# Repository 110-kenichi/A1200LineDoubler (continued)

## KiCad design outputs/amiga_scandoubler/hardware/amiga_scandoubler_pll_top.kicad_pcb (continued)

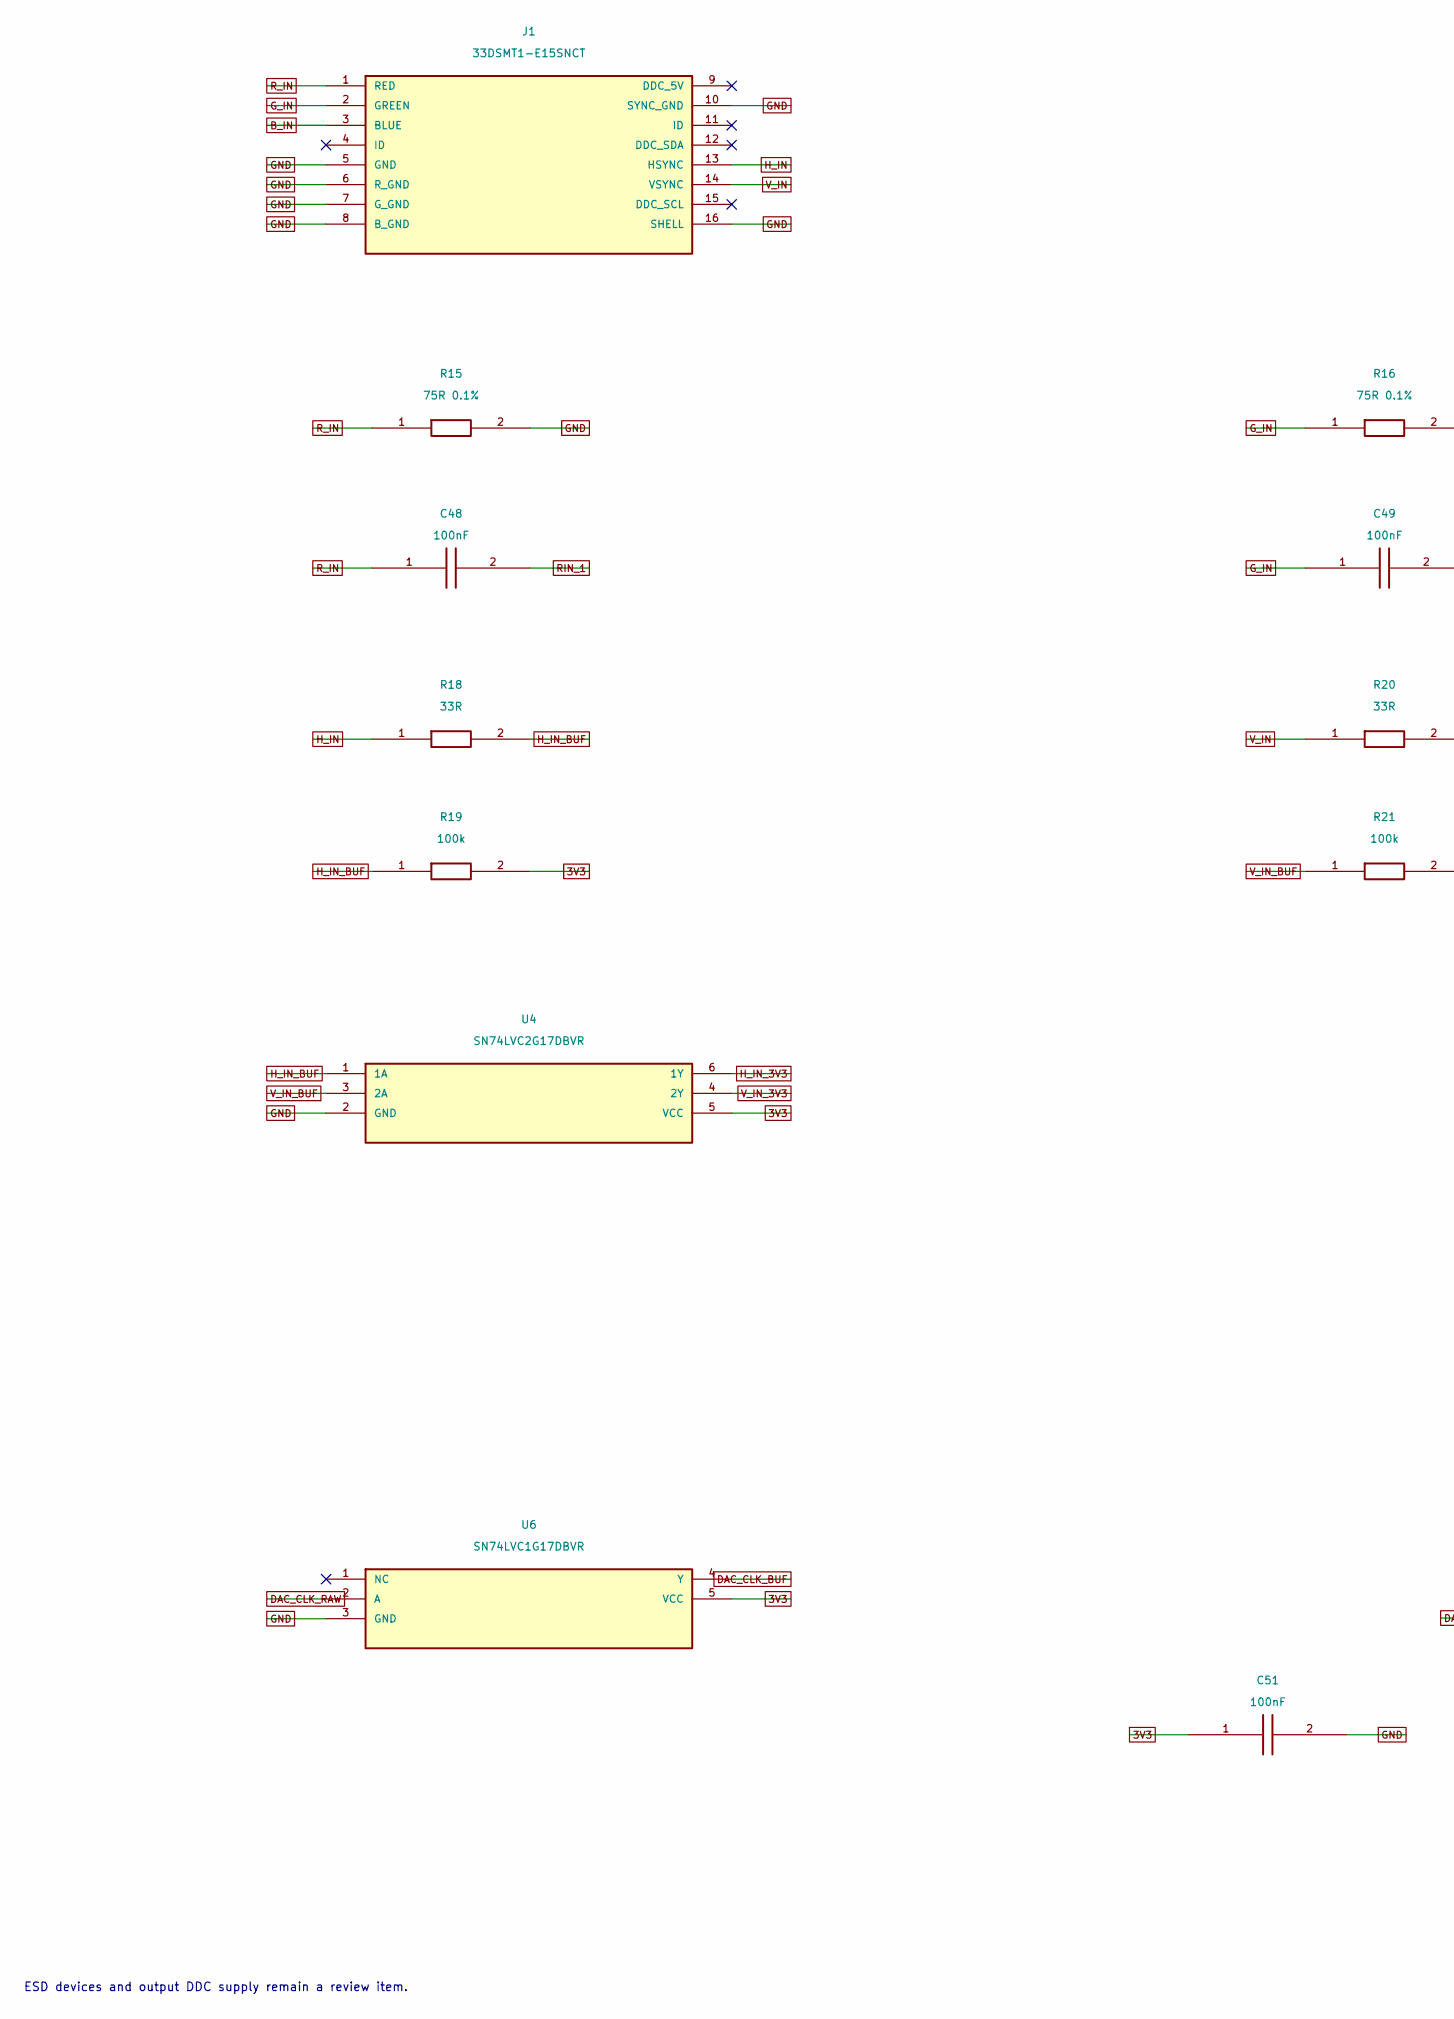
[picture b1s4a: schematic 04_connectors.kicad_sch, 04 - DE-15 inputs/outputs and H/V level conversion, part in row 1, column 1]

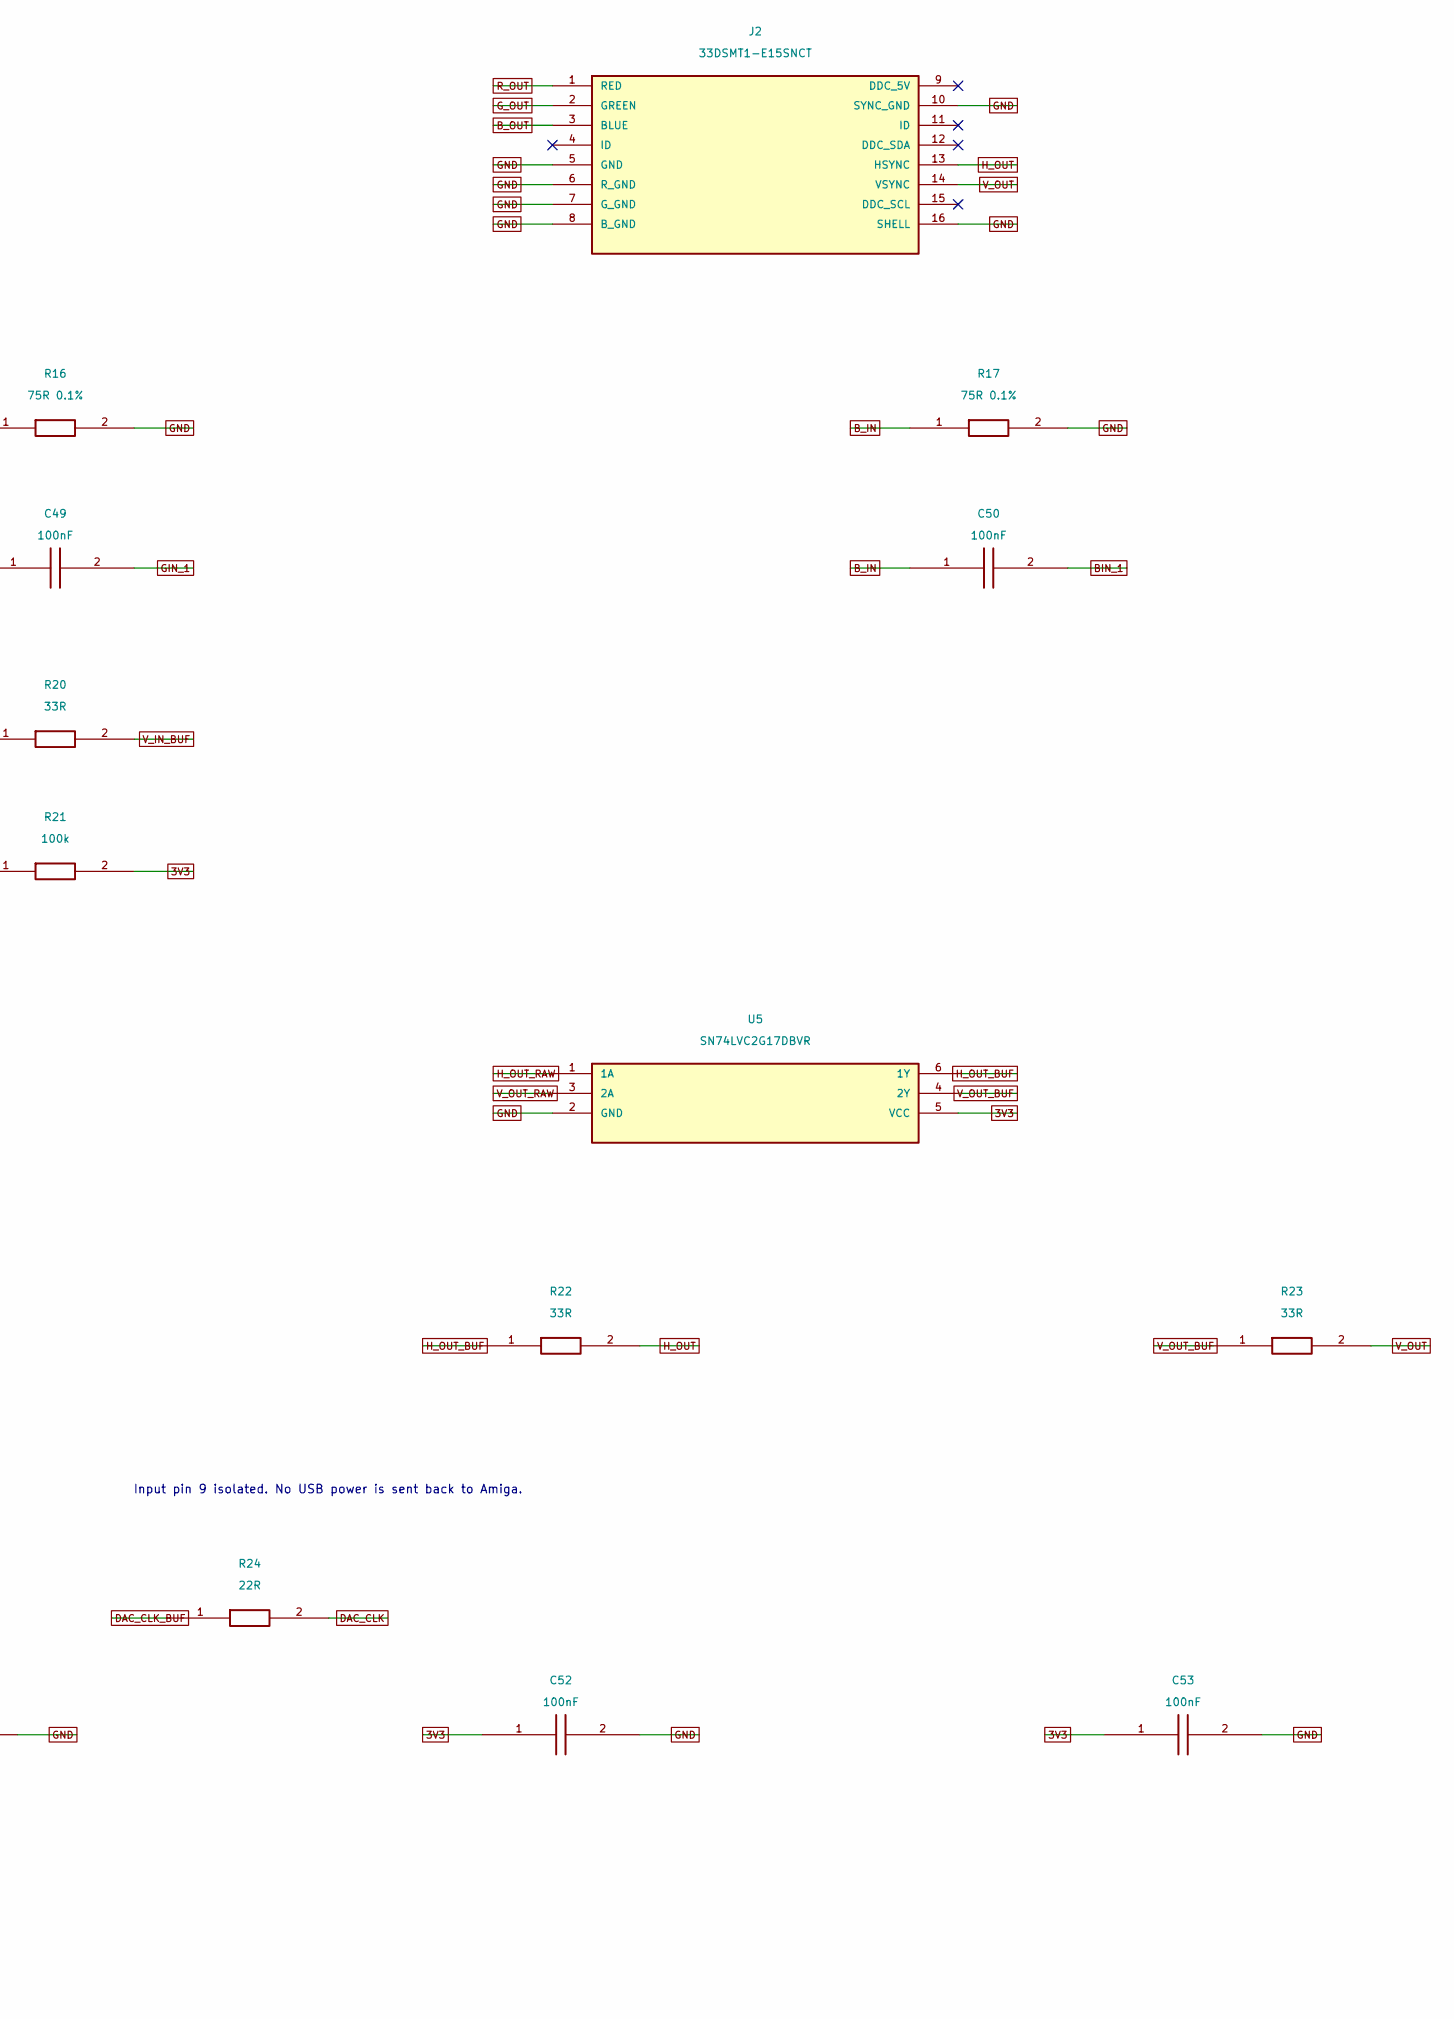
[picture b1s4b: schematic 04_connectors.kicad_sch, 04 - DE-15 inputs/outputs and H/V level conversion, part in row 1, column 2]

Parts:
C48, C49, C50, C51, C52, C53: 100nF; C_0603_1608Metric; MPN 100nF
J1, J2: 33DSMT1-E15SNCT; DE15_Conec_33DSMT1-E15SNCT; MPN 33DSMT1-E15SNCT
R15, R16, R17: 75R 0.1%; R_0603_1608Metric; MPN 75R 0.1%
R18, R20, R22, R23: 33R; R_0603_1608Metric; MPN 33R
R19, R21: 100k; R_0603_1608Metric; MPN 100k
R24: 22R; R_0603_1608Metric; MPN 22R
U4, U5: SN74LVC2G17DBVR; SOT-23-6; MPN SN74LVC2G17DBVR
U6: SN74LVC1G17DBVR; SOT-23-5; MPN SN74LVC1G17DBVR

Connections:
3V3: C51.1, C52.1, C53.1, R19.2, R21.2, U4.5 (VCC), U5.5 (VCC), U6.5 (VCC); also elsewhere on the board
BIN_1: C50.2; also elsewhere on the board
B_IN: C50.1, J1.3 (BLUE), R17.1
B_OUT: J2.3 (BLUE); also elsewhere on the board
DAC_CLK: R24.2; also elsewhere on the board
DAC_CLK_BUF: R24.1, U6.4 (Y)
DAC_CLK_RAW: U6.2 (A); also elsewhere on the board
GIN_1: C49.2; also elsewhere on the board
GND: C51.2, C52.2, C53.2, J1.5 (GND), J1.6 (R_GND), J1.7 (G_GND), J1.8 (B_GND), J1.10 (SYNC_GND), J1.16 (SHELL), J2.5 (GND), J2.6 (R_GND), J2.7 (G_GND), J2.8 (B_GND), J2.10 (SYNC_GND), J2.16 (SHELL), R15.2, R16.2, R17.2, U4.2 (GND), U5.2 (GND), U6.3 (GND); also elsewhere on the board
G_IN: C49.1, J1.2 (GREEN), R16.1
G_OUT: J2.2 (GREEN); also elsewhere on the board
H_IN: J1.13 (HSYNC), R18.1
H_IN_3V3: U4.6 (1Y); also elsewhere on the board
H_IN_BUF: R18.2, R19.1, U4.1 (1A)
H_OUT: J2.13 (HSYNC), R22.2
H_OUT_BUF: R22.1, U5.6 (1Y)
H_OUT_RAW: U5.1 (1A); also elsewhere on the board
RIN_1: C48.2; also elsewhere on the board
R_IN: C48.1, J1.1 (RED), R15.1
R_OUT: J2.1 (RED); also elsewhere on the board
V_IN: J1.14 (VSYNC), R20.1
V_IN_3V3: U4.4 (2Y); also elsewhere on the board
V_IN_BUF: R20.2, R21.1, U4.3 (2A)
V_OUT: J2.14 (VSYNC), R23.2
V_OUT_BUF: R23.1, U5.4 (2Y)
V_OUT_RAW: U5.3 (2A); also elsewhere on the board

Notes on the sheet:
Input pin 9 isolated. No USB power is sent back to Amiga.
ESD devices and output DDC supply remain a review item.

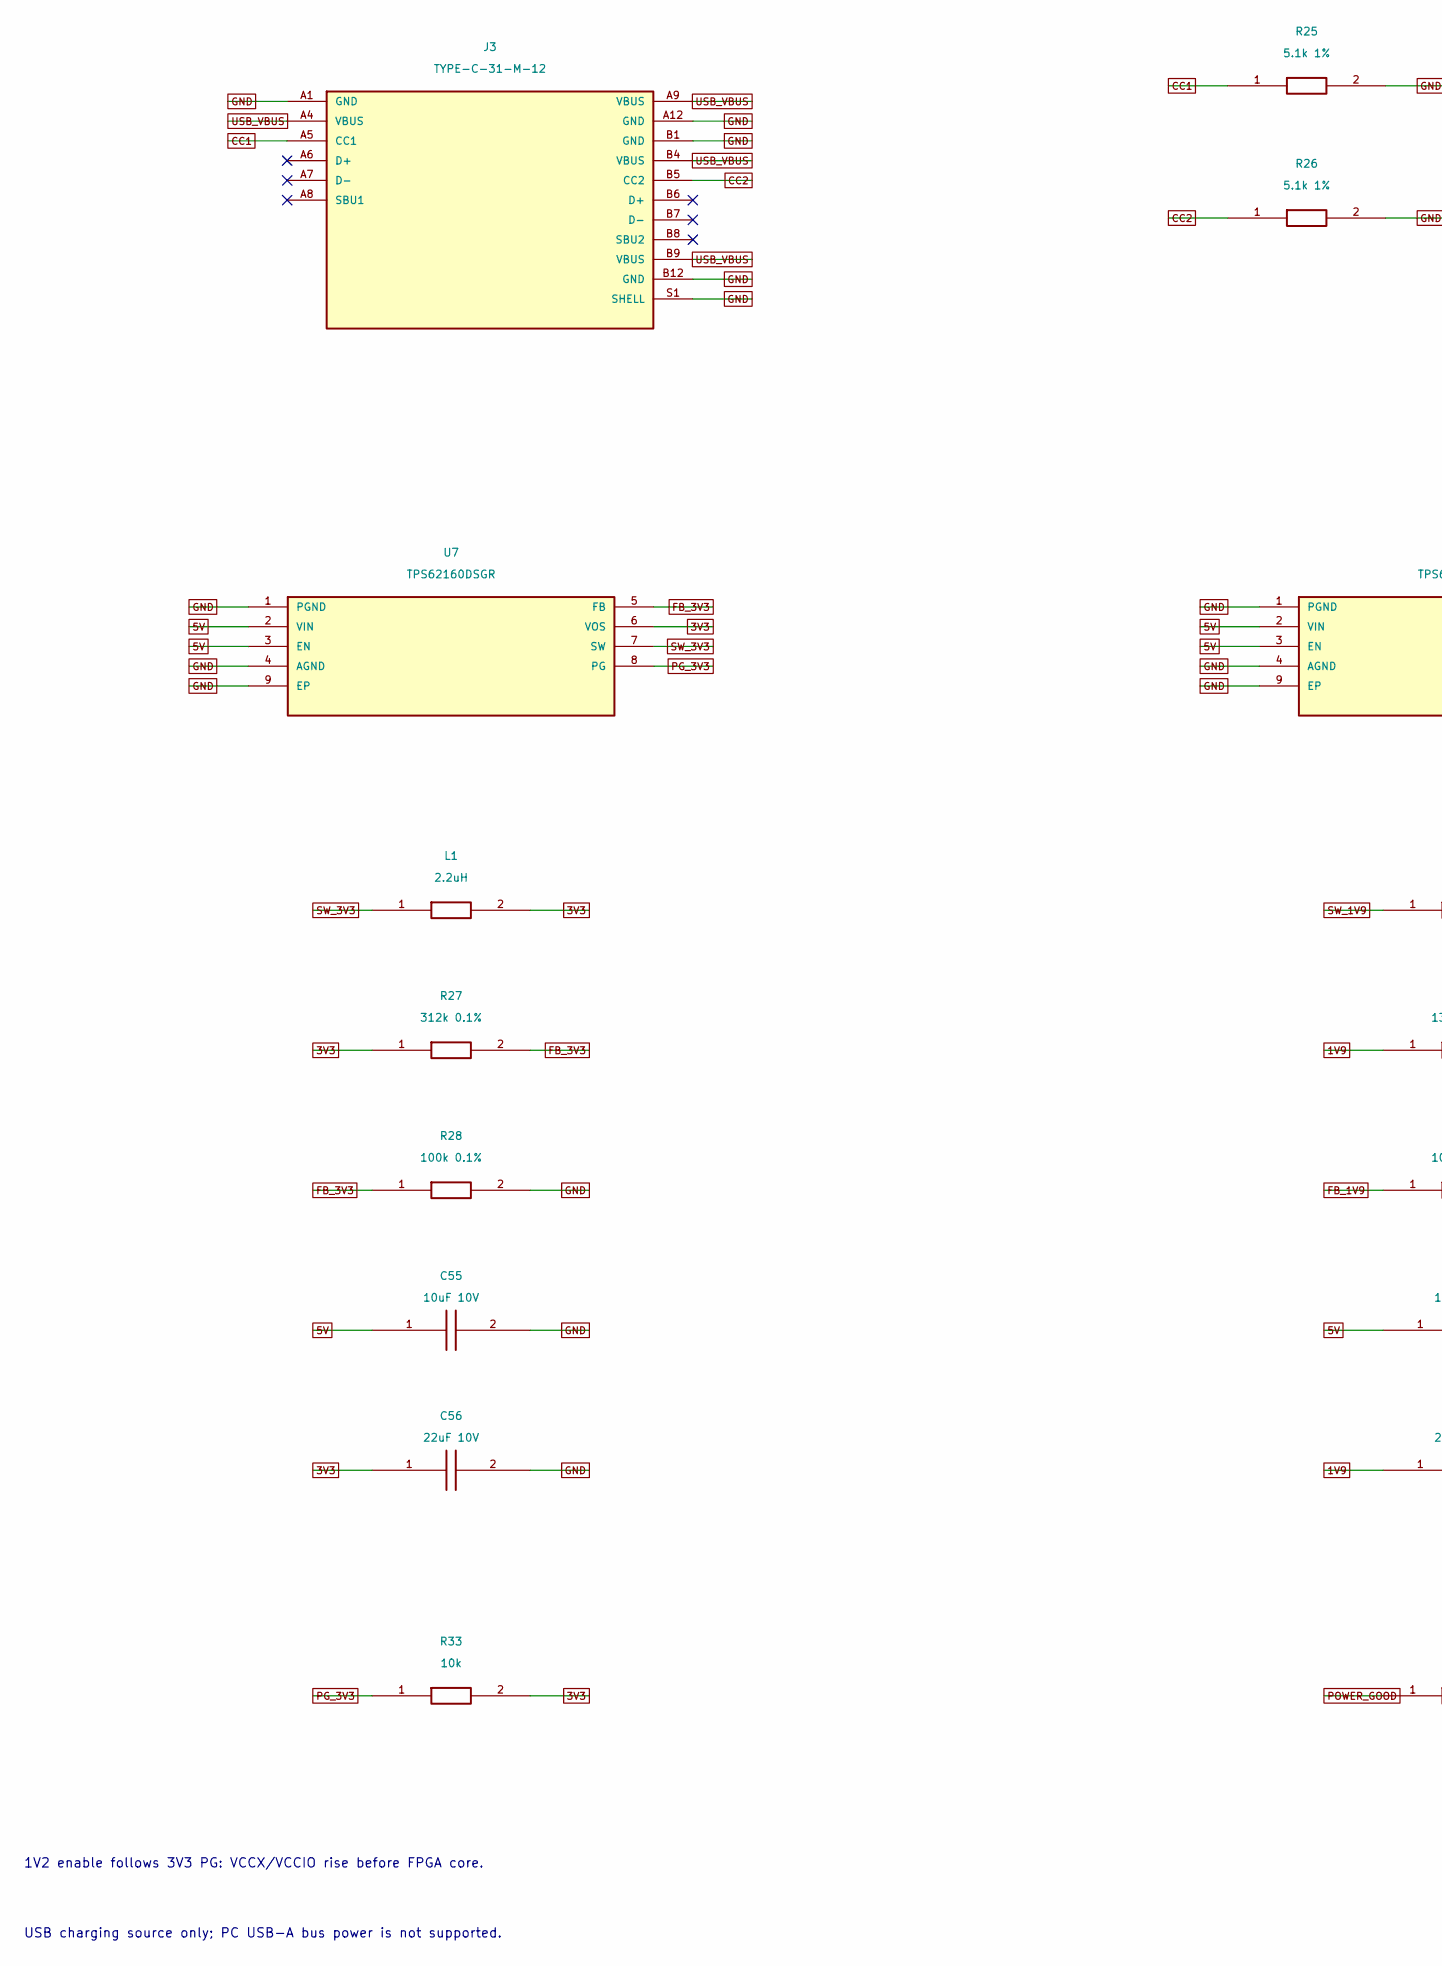
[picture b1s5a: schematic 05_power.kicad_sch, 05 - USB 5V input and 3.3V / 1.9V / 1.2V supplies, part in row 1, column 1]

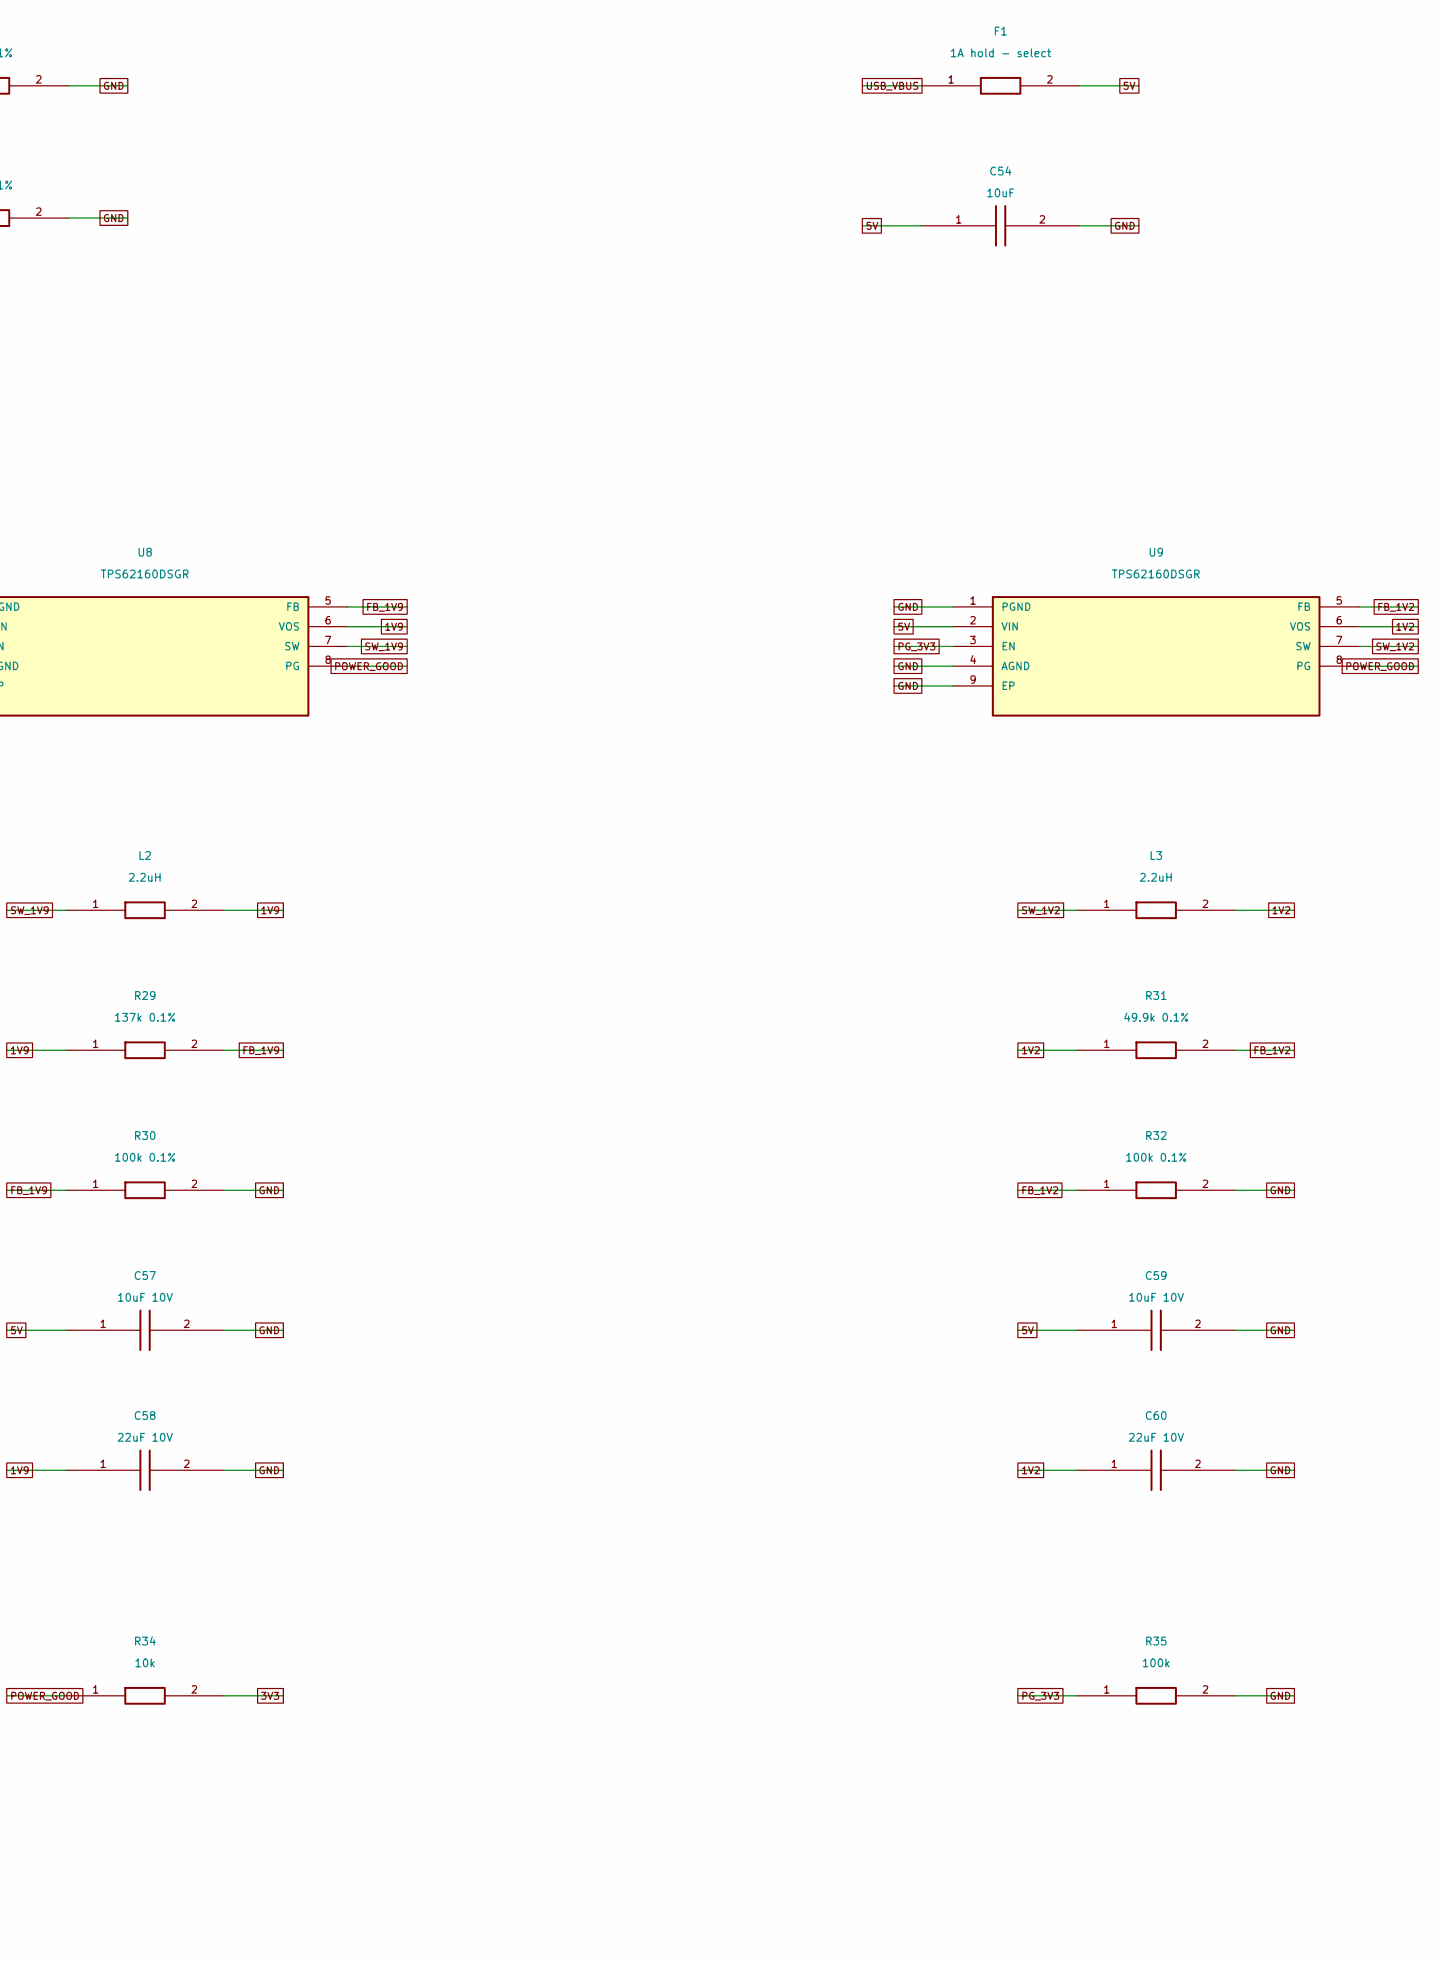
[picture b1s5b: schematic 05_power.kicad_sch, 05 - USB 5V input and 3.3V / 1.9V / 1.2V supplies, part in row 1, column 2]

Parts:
C54: 10uF; C_0805_2012Metric; MPN 10uF
C55, C57, C59: 10uF 10V; C_0805_2012Metric; MPN 10uF 10V
C56, C58, C60: 22uF 10V; C_0805_2012Metric; MPN 22uF 10V
F1: 1A hold - select; Fuse_1206_3216Metric; MPN 1A hold - select
J3: TYPE-C-31-M-12; USB_C_Receptacle_HRO_TYPE-C-31-M-12; MPN TYPE-C-31-M-12; LCSC C165948
L1, L2, L3: 2.2uH; L_TDK_VLS4012CX; MPN VLS4012CX-2R2M-1; LCSC C7413169
R25, R26: 5.1k 1%; R_0603_1608Metric; MPN 5.1k 1%
R27: 312k 0.1%; R_0603_1608Metric; MPN 312k 0.1%
R28, R30, R32: 100k 0.1%; R_0603_1608Metric; MPN 100k 0.1%
R29: 137k 0.1%; R_0603_1608Metric; MPN 137k 0.1%
R31: 49.9k 0.1%; R_0603_1608Metric; MPN 49.9k 0.1%
R33, R34: 10k; R_0603_1608Metric; MPN 10k
R35: 100k; R_0603_1608Metric; MPN 100k
U7, U8, U9: TPS62160DSGR; WSON-8-1EP_2x2mm_P0.5mm_EP0.9x1.6mm; MPN TPS62160DSGR

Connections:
1V2: C60.1, L3.2, R31.1, U9.6 (VOS); also elsewhere on the board
1V9: C58.1, L2.2, R29.1, U8.6 (VOS); also elsewhere on the board
3V3: C56.1, L1.2, R27.1, R33.2, R34.2, U7.6 (VOS); also elsewhere on the board
5V: C54.1, C55.1, C57.1, C59.1, F1.2, U7.2 (VIN), U7.3 (EN), U8.2 (VIN), U8.3 (EN), U9.2 (VIN)
CC1: J3.A5 (CC1), R25.1
CC2: J3.B5 (CC2), R26.1
FB_1V2: R31.2, R32.1, U9.5 (FB)
FB_1V9: R29.2, R30.1, U8.5 (FB)
FB_3V3: R27.2, R28.1, U7.5 (FB)
GND: C54.2, C55.2, C56.2, C57.2, C58.2, C59.2, C60.2, J3.A1 (GND), J3.A12 (GND), J3.B1 (GND), J3.B12 (GND), J3.S1 (SHELL), R25.2, R26.2, R28.2, R30.2, R32.2, R35.2, U7.1 (PGND), U7.4 (AGND), U7.9 (EP), U8.1 (PGND), U8.4 (AGND), U8.9 (EP), U9.1 (PGND), U9.4 (AGND), U9.9 (EP); also elsewhere on the board
PG_3V3: R33.1, R35.1, U7.8 (PG), U9.3 (EN)
POWER_GOOD: R34.1, U8.8 (PG), U9.8 (PG); also elsewhere on the board
SW_1V2: L3.1, U9.7 (SW)
SW_1V9: L2.1, U8.7 (SW)
SW_3V3: L1.1, U7.7 (SW)
USB_VBUS: F1.1, J3.A4 (VBUS), J3.A9 (VBUS), J3.B4 (VBUS), J3.B9 (VBUS)

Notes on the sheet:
1V2 enable follows 3V3 PG: VCCX/VCCIO rise before FPGA core.
USB charging source only; PC USB-A bus power is not supported.

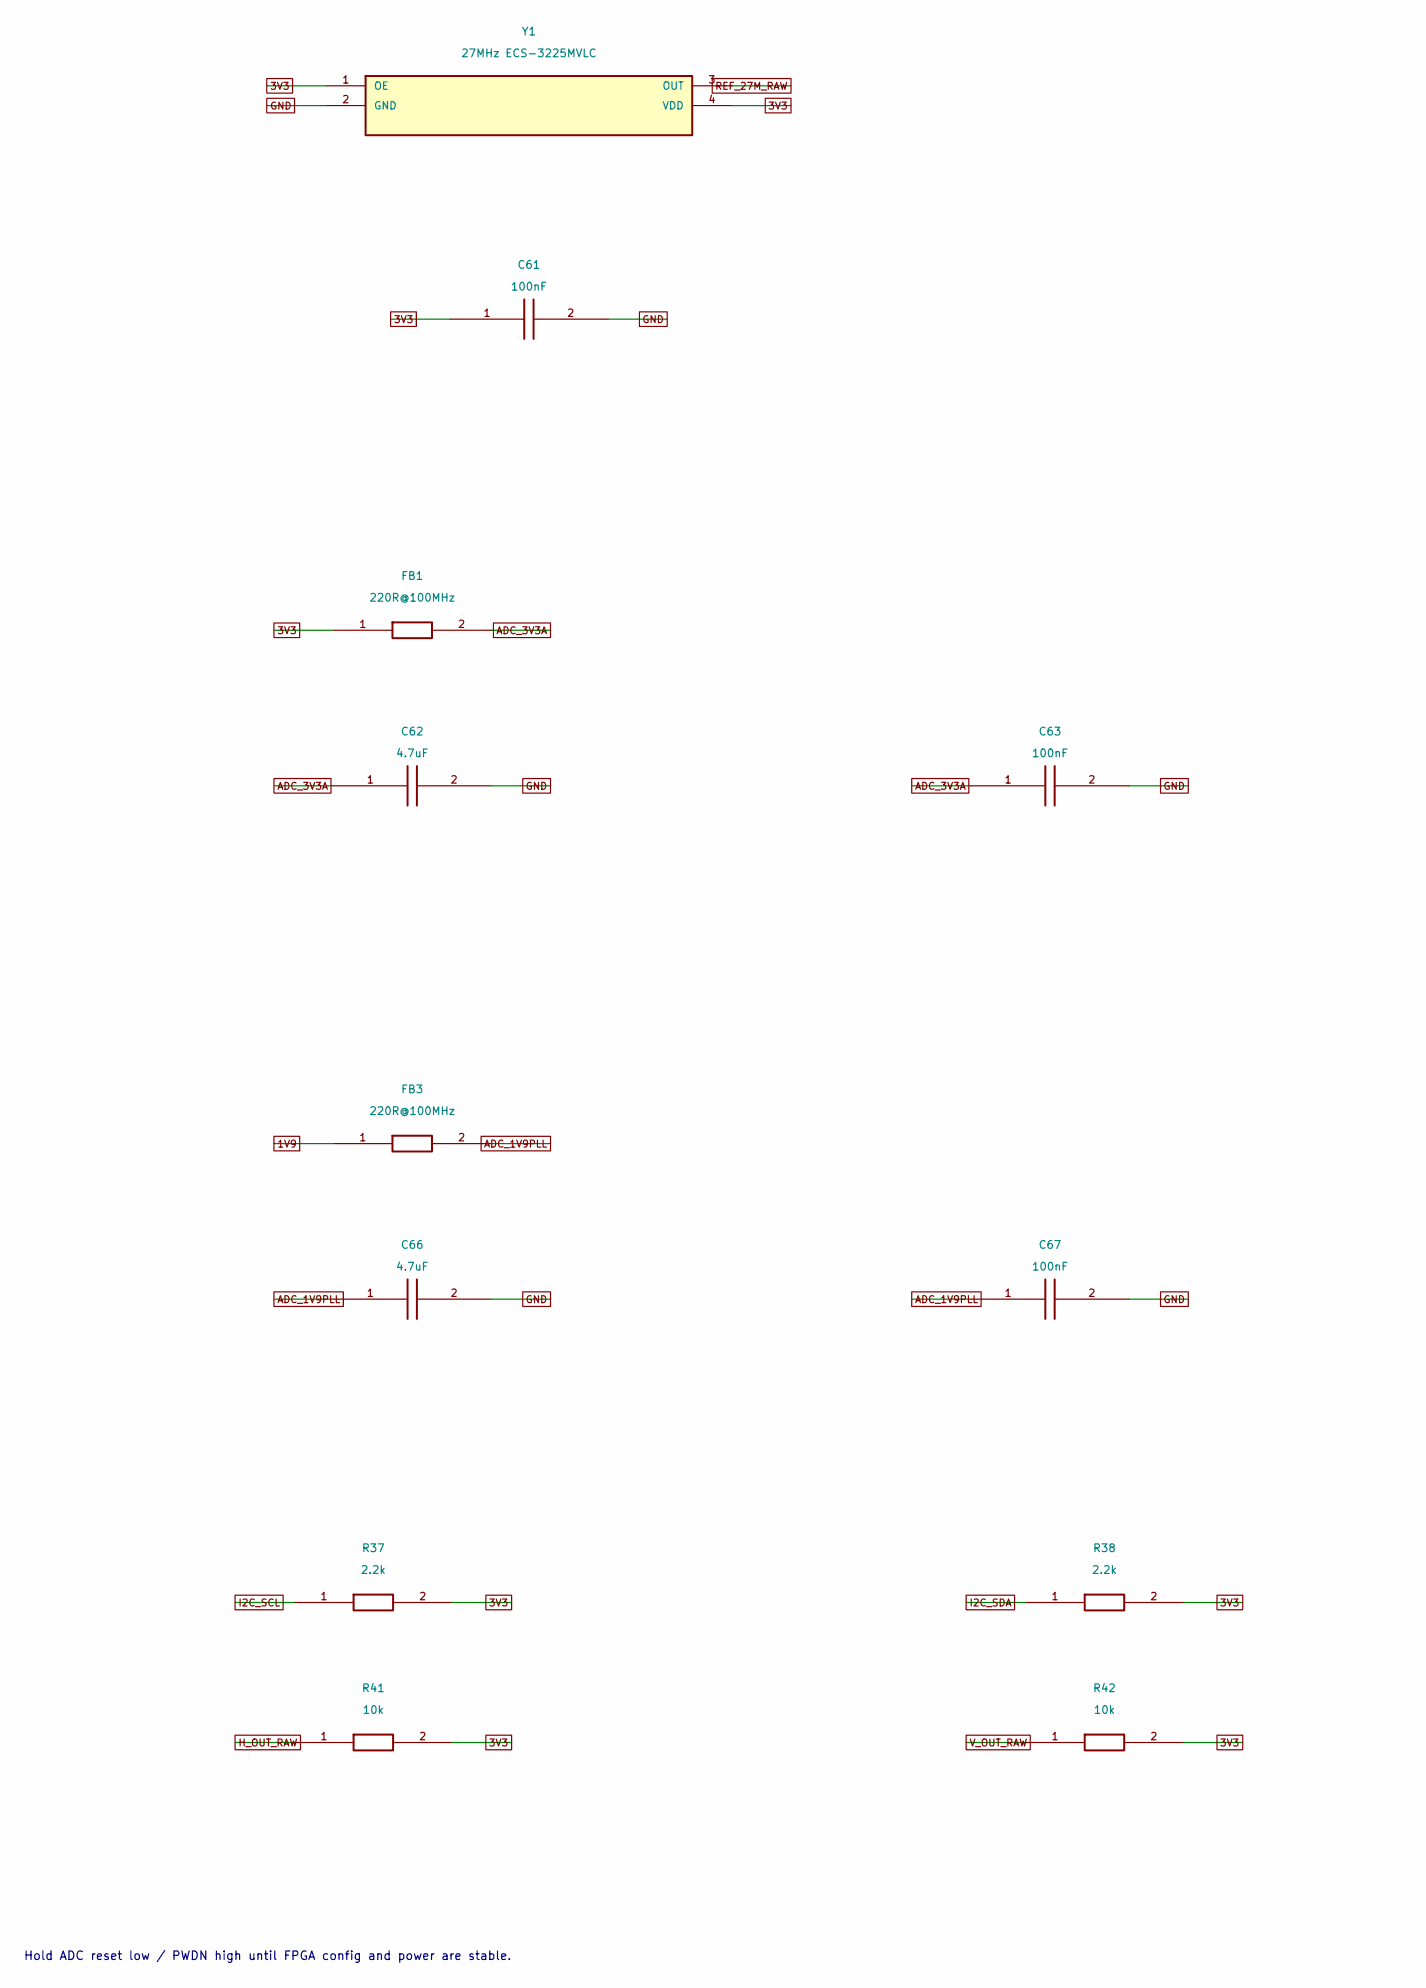
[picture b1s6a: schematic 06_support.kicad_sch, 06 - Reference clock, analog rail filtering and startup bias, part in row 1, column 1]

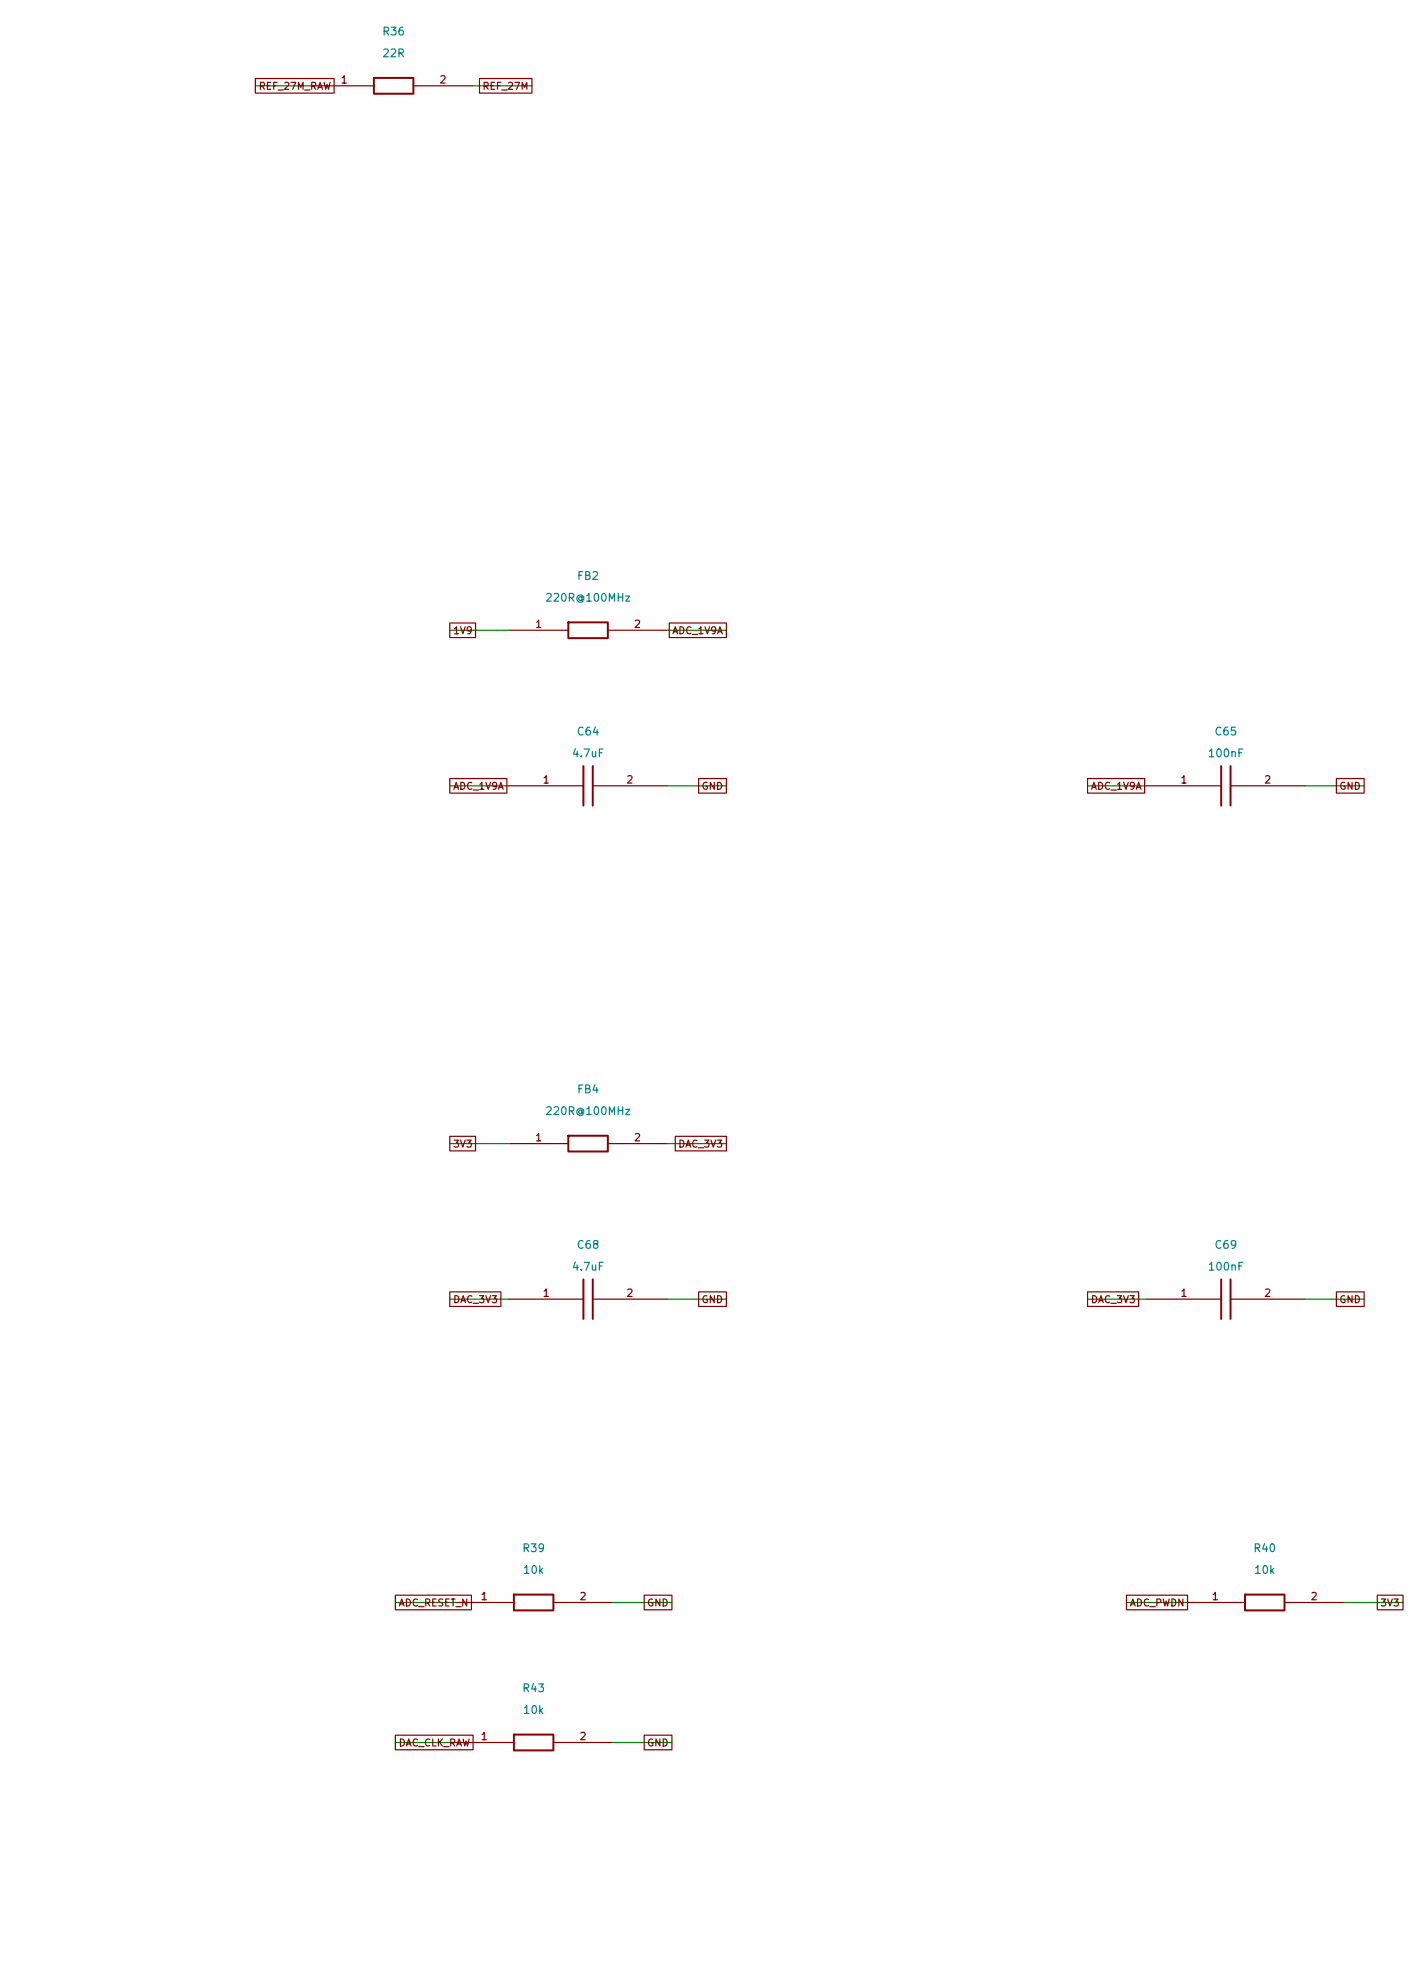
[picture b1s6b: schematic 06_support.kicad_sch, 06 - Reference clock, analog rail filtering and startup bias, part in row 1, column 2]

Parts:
C61, C63, C65, C67, C69: 100nF; C_0603_1608Metric; MPN 100nF
C62, C64, C66, C68: 4.7uF; C_0805_2012Metric; MPN 4.7uF
FB1, FB2, FB3, FB4: 220R@100MHz; L_0603_1608Metric; MPN 220R@100MHz
R36: 22R; R_0603_1608Metric; MPN 22R
R37, R38: 2.2k; R_0603_1608Metric; MPN 2.2k
R39, R40, R41, R42, R43: 10k; R_0603_1608Metric; MPN 10k
Y1: 27MHz ECS-3225MVLC; OSC_ECS-3225MVLC_3.2x2.5; MPN ECS-3225MVLC-270-CN-TR

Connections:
1V9: FB2.1, FB3.1; also elsewhere on the board
3V3: C61.1, FB1.1, FB4.1, R37.2, R38.2, R40.2, R41.2, R42.2, Y1.1 (OE), Y1.4 (VDD); also elsewhere on the board
ADC_1V9A: C64.1, C65.1, FB2.2; also elsewhere on the board
ADC_1V9PLL: C66.1, C67.1, FB3.2; also elsewhere on the board
ADC_3V3A: C62.1, C63.1, FB1.2; also elsewhere on the board
ADC_PWDN: R40.1; also elsewhere on the board
ADC_RESET_N: R39.1; also elsewhere on the board
DAC_3V3: C68.1, C69.1, FB4.2; also elsewhere on the board
DAC_CLK_RAW: R43.1; also elsewhere on the board
GND: C61.2, C62.2, C63.2, C64.2, C65.2, C66.2, C67.2, C68.2, C69.2, R39.2, R43.2, Y1.2 (GND); also elsewhere on the board
H_OUT_RAW: R41.1; also elsewhere on the board
I2C_SCL: R37.1; also elsewhere on the board
I2C_SDA: R38.1; also elsewhere on the board
REF_27M: R36.2; also elsewhere on the board
REF_27M_RAW: R36.1, Y1.3 (OUT)
V_OUT_RAW: R42.1; also elsewhere on the board

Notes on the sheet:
Hold ADC reset low / PWDN high until FPGA config and power are stable.

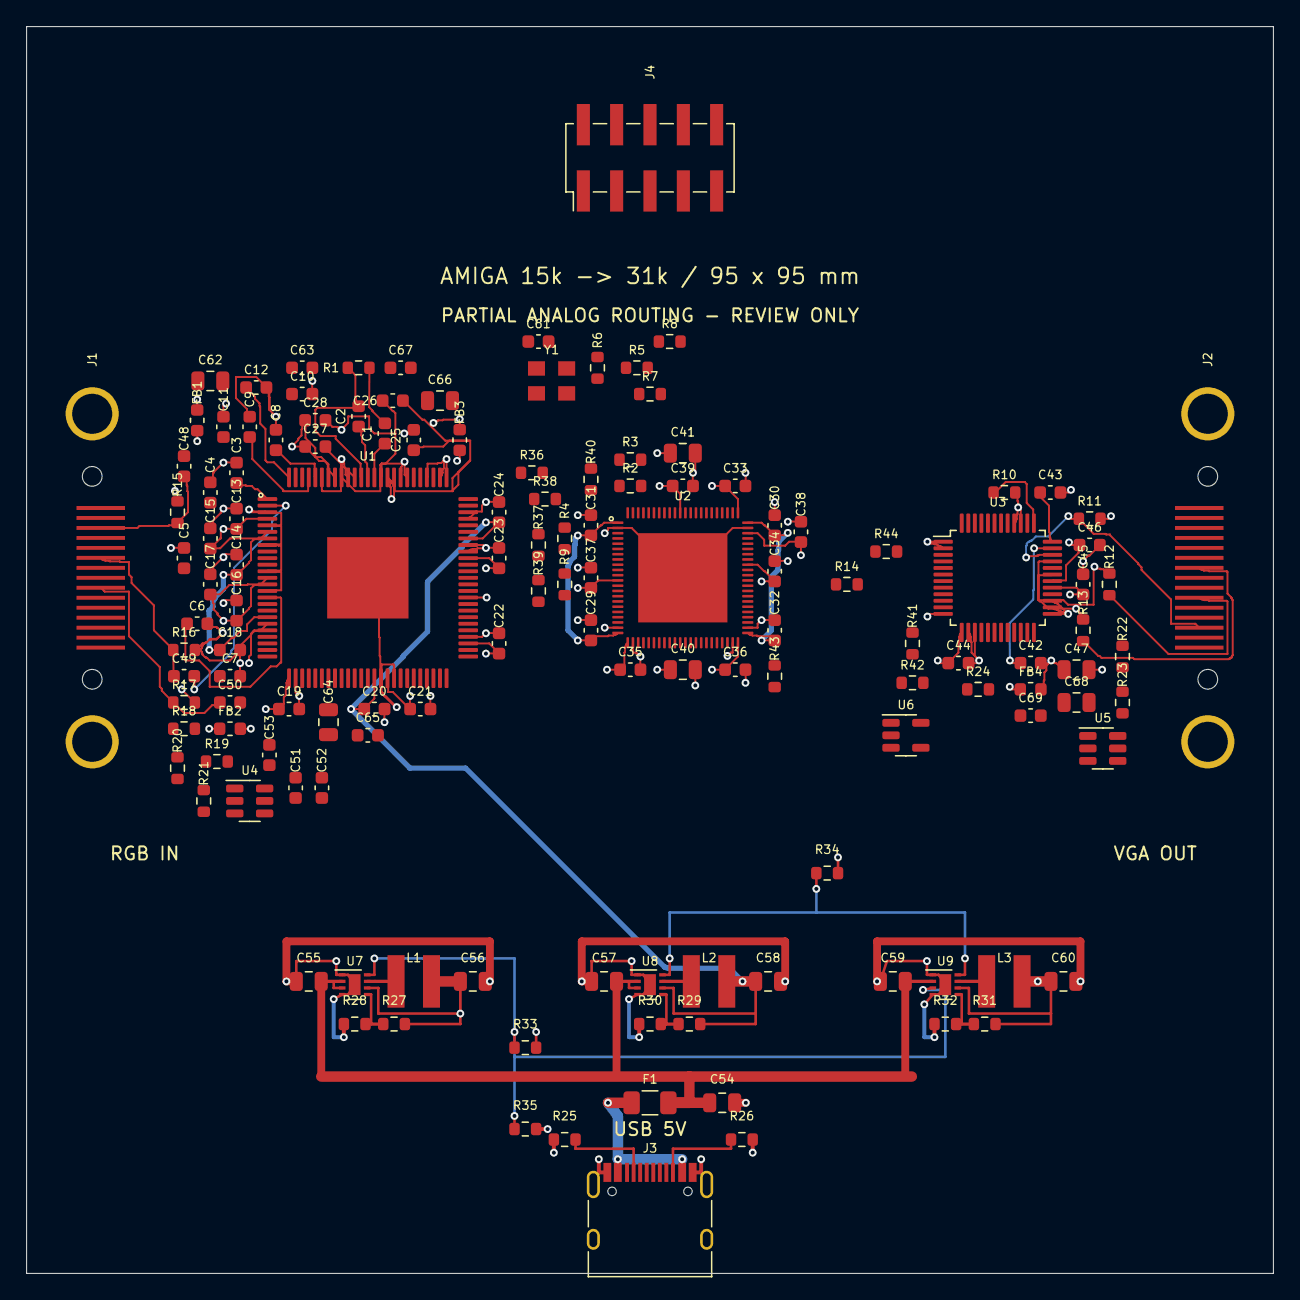
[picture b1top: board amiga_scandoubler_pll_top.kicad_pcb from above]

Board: 4 copper layers, 95.0 x 95.0 mm, 135 parts (0 on the bottom side), 129 nets.
